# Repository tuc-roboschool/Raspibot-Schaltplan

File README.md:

# Raspibot-Schaltplan
Schaltplan für den TUC-Raspibot

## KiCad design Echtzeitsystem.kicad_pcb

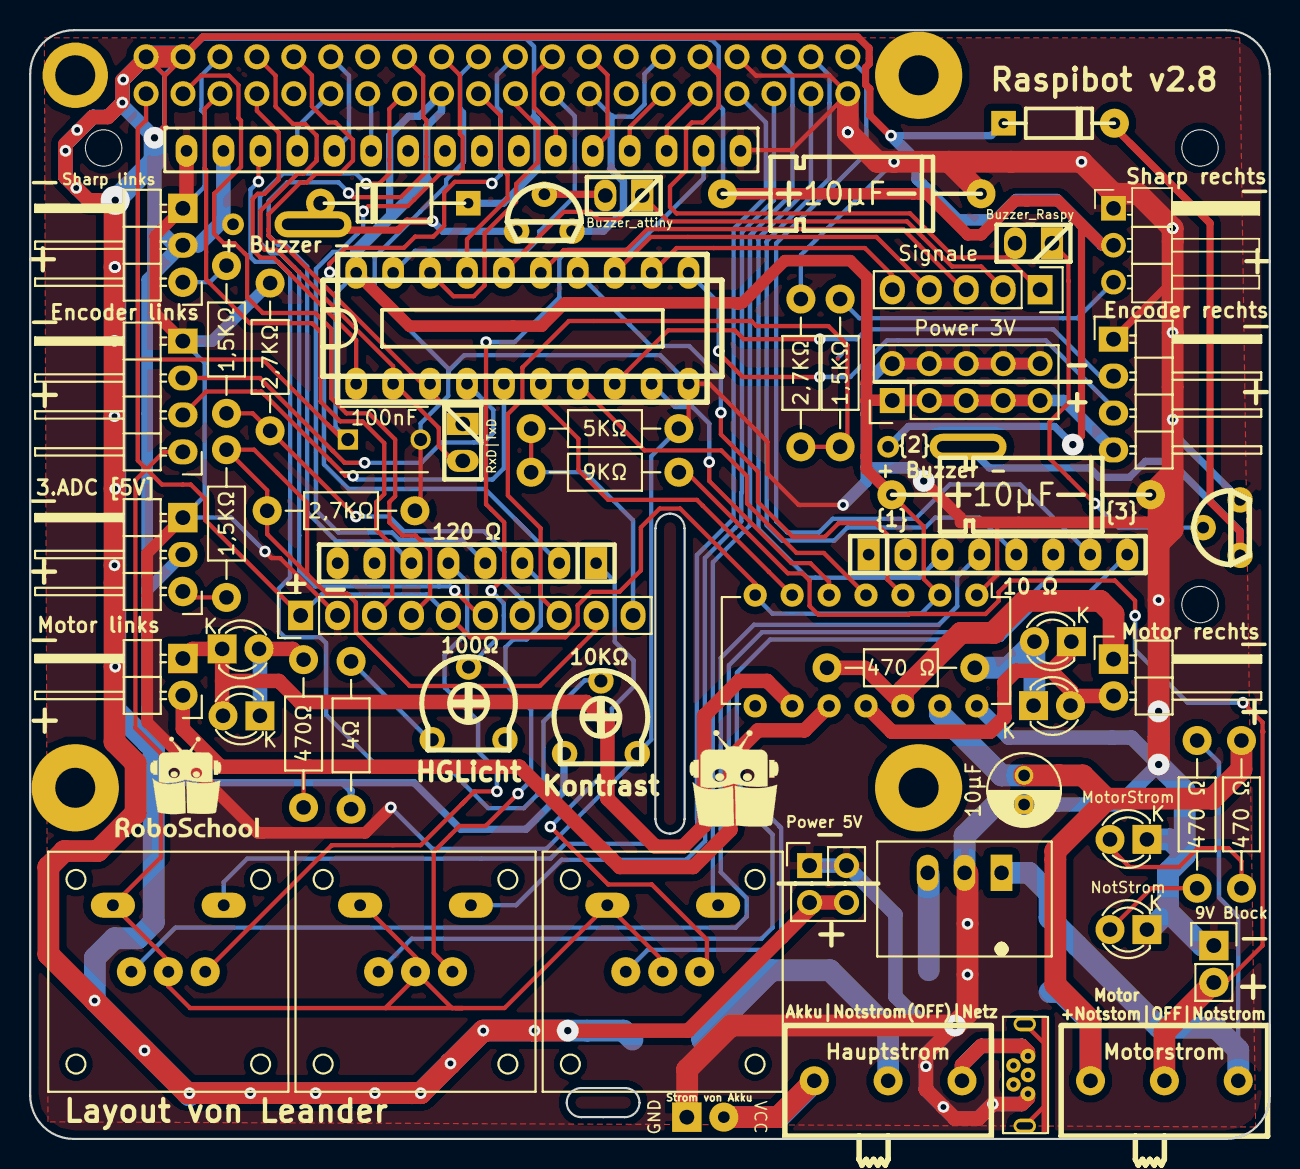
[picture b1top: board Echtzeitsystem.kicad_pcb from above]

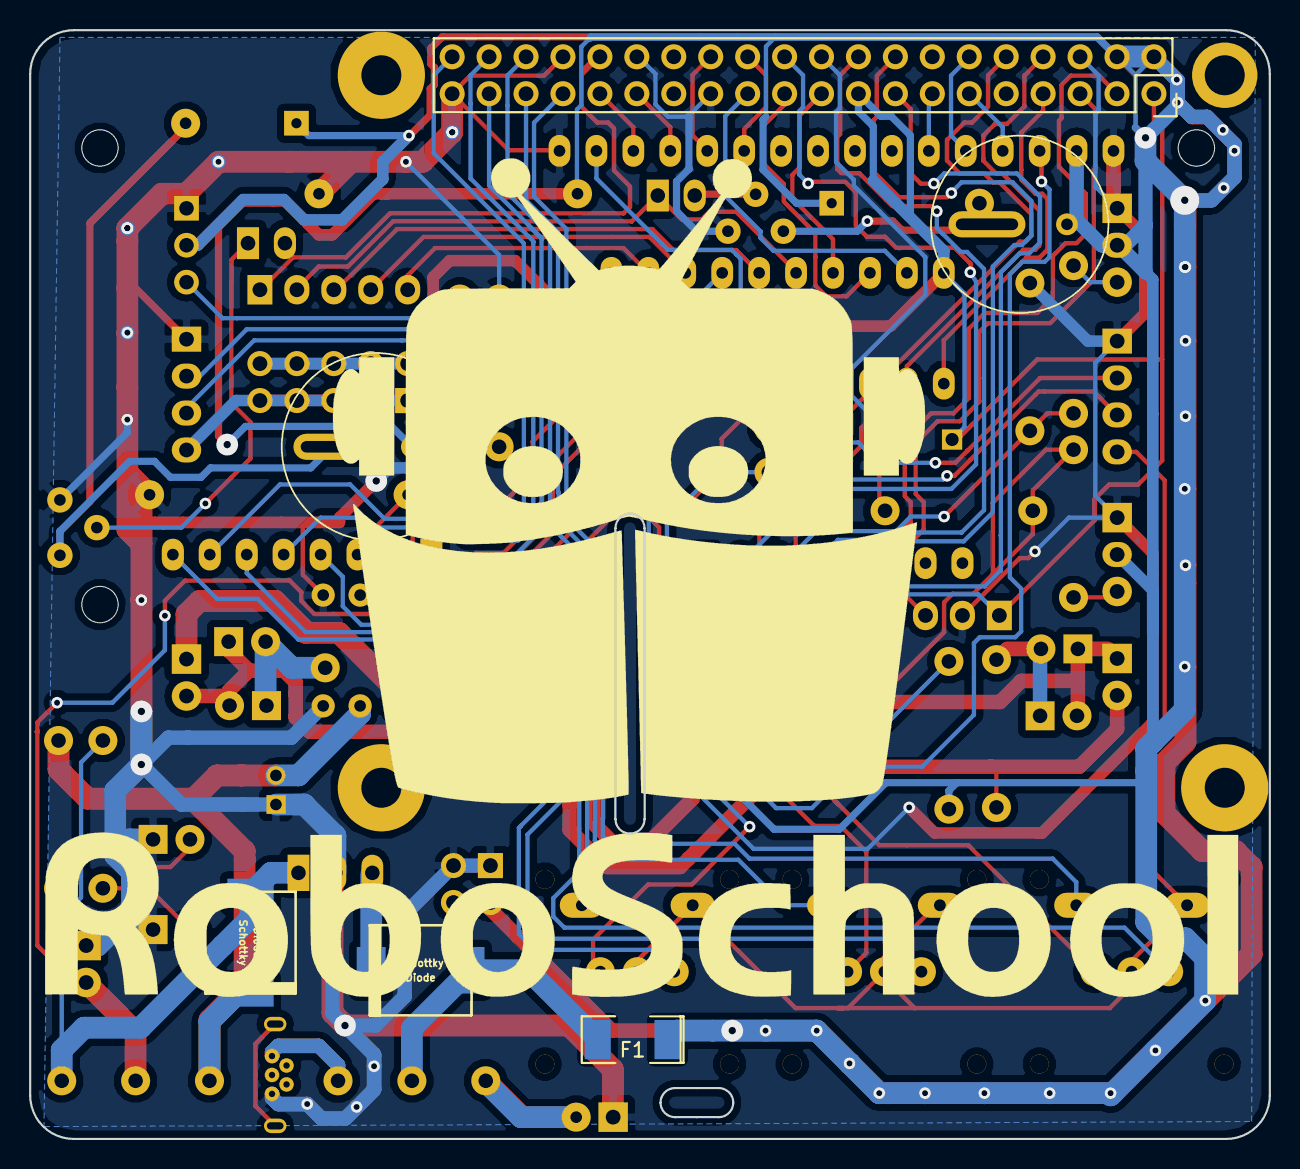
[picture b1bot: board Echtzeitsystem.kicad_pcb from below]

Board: 2 copper layers, 85.2 x 76.2 mm, 63 parts (7 on the bottom side), 76 nets.

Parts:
3.3VPower1: Power 3V; Pin_Header_Straight_2x05
12VAnschluss1: CONN_01X02; Pin_Header_Straight_1x02
AkkuStrom1: Strom von Akku; SolderWirePad_2x_0-8mmDrill
Attiny1: ATTINY2313A-P; dil_20-300_socket
BZ1: Buzzer; MagneticBuzzer_ProSignal_ABT-410-RC
BZ2: Buzzer; Buzzer_12,7_5mm
C1, C2: 10µF; CPA_5x11MM
C3: 100nF; C_Disc_D6_P5
C5: 10µF; C_Radial_D5_L11_P2
D1, D2, D3: LED_Button2_RG; SW_PUSH-LED-WS-PBTL
D4: NotStrom; LED-3MM
D5, D6, D7, D8, D9: MotorStrom; LED-3MM
D10: DIODE; diode_do41
D11: DIODE; diode_do35
EncoderLinks1: CONN_01X02; Pin_Header_Angled_1x04
EncoderRechts1: CONN_01X02; Pin_Header_Angled_1x04_left
F1: FP_Small; SMD-2010_Pol
J1: Buzzer_attiny; pin_strip_2
J2: Buzzer_Raspy; pin_strip_2
JRXTX: RxD|TxD; pin_strip_2
MotorLinksAusgang1: CONN_01X02; Pin_Header_Angled_1x02
MotorRechtsAusgang1: CONN_01X02; Pin_Header_Angled_1x02_left
Motordriver1: DRV8835; DIP-14_W7.62mm
Netz1: NetzStrom; USB_Micro-B-Stehend
P0: RasPI_IO_Header_B+; Socket_Strip_Straight_2x20
P9: CONN_01X03; Pin_Header_Angled_1x03_left
PololuDisplay1: CONN_02X07; lcd_16x2
Power5: Power 5V; Pin_Header_Straight_2x02
Q1, Q2: Q_NPN_BCE; to92_3
R1, R16, R17: 470 Ω; Resistor_Horizontal_RM10mm
R1-10K1: Kontrast; trimmer_piher_pt6xv
R2: 4Ω; Resistor_Horizontal_RM10mm
R3, R5, R7: 1,5KΩ; Resistor_Horizontal_RM10mm
R4, R6, R8: 2,7KΩ; Resistor_Horizontal_RM10mm
R18: 470Ω; Resistor_Horizontal_RM10mm
R19: 9KΩ; Resistor_Horizontal_RM10mm
R20: 5KΩ; Resistor_Horizontal_RM10mm
R100Ω-200: HGLicht; trimmer_piher_pt6xv
R-GLED2: 10 Ω; r-sil_8
R-RLED2: 120 Ω; r-sil_8
SHARP_ADC0: ADS1015; Socket_Strip_Straight_1x10
SW1, SW2: Switch_Motor_Power; switch_25539N
Schottky: Diode; do214ab
Schottky#2: Diode; do214ab
Sharp_left1: CONN_01X03; Pin_Header_Angled_1x03_left
Sharpright1: CONN_01X03; Pin_Header_Angled_1x03_Pitch2.54mm
Signale1: Signale; Pin_Header_Straight_1x05
U1: MCP1754ST-1802E/MB; DCDC-Conv_TRACO_TSR-1

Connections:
9V-Notstrom: R1.1, SW1.3, Schottky#2.1, U1.1
+3.3V: 3.3VPower1.1, 3.3VPower1.3, 3.3VPower1.5, 3.3VPower1.7, 3.3VPower1.9, Attiny1.20, C1.1, C3.1, D1.2, D1.LC, D2.2, D2.LC, D3.2, D3.LC, EncoderLinks1.4, EncoderRechts1.1, Motordriver1.2, Motordriver1.7, P0.1, P0.17, SHARP_ADC0.1, SHARP_ADC0.5
+5V: BZ1.1, BZ2.1, C2.1, D10.1, D11.1, F1.1, P0.2, P0.4, P9.2, PololuDisplay1.2, Power5.3, Power5.4, R1-10K1.1, R2.2, Sharp_left1.2, Sharpright1.2
+9V: 12VAnschluss1.2, R19.2, SW1.2
/ACD/Batteriespannung?: R19.1, R20.1, SHARP_ADC0.10
/ACD/RechterSharp: R7.1, R8.1, SHARP_ADC0.7
/ACD/linkerSharp: R3.1, R4.1, SHARP_ADC0.8
/AkkuVcc: AkkuStrom1.1, SW2.1
/Attiny/OUTA: Attiny1.11, EncoderLinks1.3
/Attiny/OUTA-R: Attiny1.5, EncoderRechts1.2
/Attiny/OUTB: Attiny1.8, EncoderLinks1.2
/Attiny/OUTB-R: Attiny1.4, EncoderRechts1.3
/LED-Taster/Green-3,2V-1: D1.L2, R-GLED2.6
/LED-Taster/Green-3,2V-2: D2.L2, R-GLED2.4
/LED-Taster/Red-2.4V,2: D2.L1, R-RLED2.5
/LED-Taster/Red-2.4V-1: D1.L1, R-RLED2.3
/LED-Taster/Red-2.4V-3: D3.L1, R-RLED2.1
/NetzVcc: Netz1.1, SW2.3
ALRT-ADC: P0.15, SHARP_ADC0.6
Attiny-Reset: Attiny1.1, P0.7
Attiny-RxD: Attiny1.2, P0.8
Attiny-TxD: Attiny1.3, P0.10
FreierGPIO: J2.2, JRXTX.2, P0.32, Signale1.1
GND: 3.3VPower1.2, 3.3VPower1.4, 3.3VPower1.6, 3.3VPower1.8, 3.3VPower1.10, 12VAnschluss1.1, AkkuStrom1.2, Attiny1.10, C1.2, C2.2, C3.2, C5.2, D4.1, D5.1, EncoderLinks1.1, EncoderRechts1.4, Motordriver1.1, Motordriver1.14, Netz1.5, P0.6, P0.9, P0.14, P0.20, P0.25, P0.30, P0.34, P0.39, P9.3, PololuDisplay1.1, PololuDisplay1.16, Power5.1, Power5.2, Q1.1, Q2.1, R1-10K1.3, R4.2, R6.2, R8.2, R20.2, SHARP_ADC0.2, Sharp_left1.3, Sharpright1.1, U1.2
LEDTASTER1-GREEN: P0.38, R-GLED2.5
LEDTASTER1-RED: P0.18, R-RLED2.4
LEDTASTER1-TASTER: D1.1, P0.35
LEDTASTER2-GREEN: P0.37, R-GLED2.3
LEDTASTER2-RED: P0.16, R-RLED2.6
LEDTASTER2-TASTER: D2.1, P0.33
LEDTASTER3-GREEN: P0.40, R-GLED2.7
LEDTASTER3-RED: P0.22, R-RLED2.2
LEDTASTER3-TASTER: D3.1, P0.36
MISO: Attiny1.18, P0.21
MOSI: Attiny1.17, P0.19
MotorLDIR: Attiny1.7, Motordriver1.4
MotorLPWM: Attiny1.14, Motordriver1.3
MotorRDIR: Attiny1.6, Motordriver1.6
MotorRPWM: Attiny1.9, Motordriver1.5
unnamed: Attiny1.12, Signale1.5
unnamed: Attiny1.13, Signale1.4
unnamed: Attiny1.15, Signale1.3
unnamed: Attiny1.16, J1.1, Signale1.2
unnamed: BZ1.2, D10.2, Q1.3
unnamed: BZ2.2, D11.2, Q2.3
unnamed: C5.1, Motordriver1.13, R16.1, SW1.1, Schottky#2.2
unnamed: D3.L2, R-GLED2.8
unnamed: D4.2, R1.2
unnamed: D5.2, R16.2
unnamed: D6.1, D7.2, MotorLinksAusgang1.2, Motordriver1.11
unnamed: D6.2, D7.1, R17.2
unnamed: D8.1, D9.2, MotorRechtsAusgang1.2, Motordriver1.9
unnamed: D8.2, D9.1, R18.2
unnamed: F1.2, SW2.2, Schottky.1
unnamed: J1.2, Q1.2
unnamed: J2.1, JRXTX.1, Q2.2
unnamed: MotorLinksAusgang1.1, Motordriver1.12, R17.1
unnamed: MotorRechtsAusgang1.1, Motordriver1.10, R18.1
unnamed: P0.11, PololuDisplay1.4
unnamed: P0.12, PololuDisplay1.5
unnamed: P0.13, PololuDisplay1.6
unnamed: P0.24, PololuDisplay1.11
unnamed: P0.26, PololuDisplay1.12
unnamed: P0.29, PololuDisplay1.13
unnamed: P0.31, PololuDisplay1.14
unnamed: P9.1, R5.2
unnamed: PololuDisplay1.3, R1-10K1.2
unnamed: PololuDisplay1.15, R100Ω-200.2
unnamed: R3.2, Sharpright1.3
unnamed: R5.1, R6.1, SHARP_ADC0.9
unnamed: R7.2, Sharp_left1.1
unnamed: R2.1, R100Ω-200.1
unnamed: Schottky.2, U1.3
SCK: Attiny1.19, P0.23
SCL-ADC: P0.5, SHARP_ADC0.3
SDA-ADC: P0.3, SHARP_ADC0.4

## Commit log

2017-06-24 Schaltplan v2.8
